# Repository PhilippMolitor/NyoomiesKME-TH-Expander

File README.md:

# NyoomiesKME TH Expander
An expander board for the [Nyoomies](https://github.com/comradef191/NyoomiesKME) klipper motor expansion.

# BOM
1. 4x 1206 2.2k 1% resistor
2. 4x 1206 10uF capacitor
3. 4x JST-SH 2pin socket
4. 1x 2.54mm 2x4pin socket

# Klipper configuration
See the [example configuration](nyoomies-th-expander.cfg) for reference.

# Schematic

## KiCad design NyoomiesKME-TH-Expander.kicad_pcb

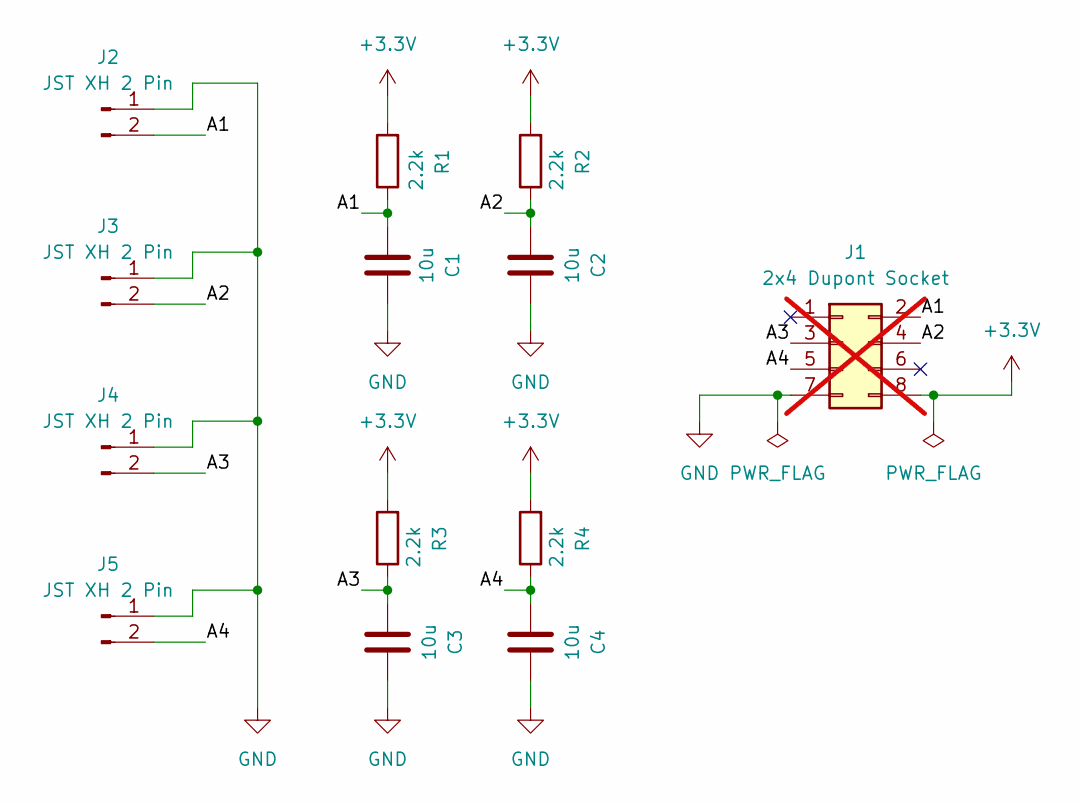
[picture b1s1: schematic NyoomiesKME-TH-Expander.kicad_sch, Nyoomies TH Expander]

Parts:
C1, C2, C3, C4: 10u; C_1206_3216Metric; LCSC Part # C47971
J1: 2x4 Dupont Socket; PinSocket_2x04_P2.54mm_Vertical; not fitted
J2, J3, J4, J5: JST XH 2 Pin; JST_XH_B2B-XH-A_1x02_P2.50mm_Vertical; LCSC Part # C158012
R1, R2, R3, R4: 2.2k; R_1206_3216Metric; LCSC Part # C311944

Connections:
+3.3V: J1.8, R1.2, R2.2, R3.2, R4.2
/A1: C1.1, J1.2, J2.2, R1.1
/A2: C2.1, J1.4, J3.2, R2.1
/A3: C3.1, J1.3, J4.2, R3.1
/A4: C4.1, J1.5, J5.2, R4.1
GND: C1.2, C2.2, C3.2, C4.2, J1.7, J2.1, J3.1, J4.1, J5.1

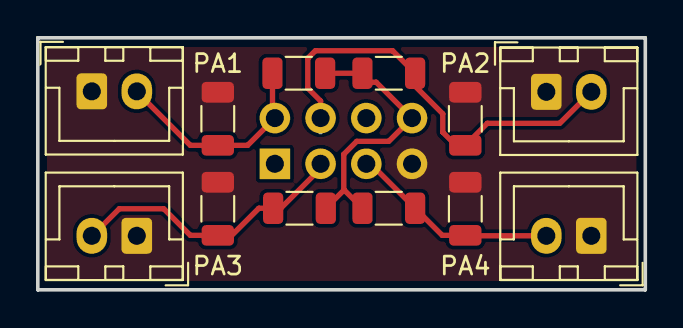
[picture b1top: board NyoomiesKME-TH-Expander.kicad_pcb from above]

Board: 2 copper layers, 33.8 x 14.0 mm, 13 parts (1 on the bottom side), 6 nets.

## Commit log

2024-07-11 smaller routing fixes, relocate R3 R4
2024-07-11 rev 0.2: add filter caps
2024-07-11 switch to 2.2k, fix pcb DRC
2024-07-11 rename to TH Expander
2024-07-11 add sheet info to pcb doc
2024-07-11 add example config for klipper
2024-07-11 fix capacitor part no.
2024-07-11 add gerber_to_order
2024-07-14 switch to 2.2k resistors for example config
2024-07-19 use filtering caps correctly and use labels instead of global labels
2024-07-19 minor routing improvements
2024-07-19 switch to unpolarized caps
2024-08-02 add readme
2024-08-06 rev 0.3 - change header position, improve silkscreen
